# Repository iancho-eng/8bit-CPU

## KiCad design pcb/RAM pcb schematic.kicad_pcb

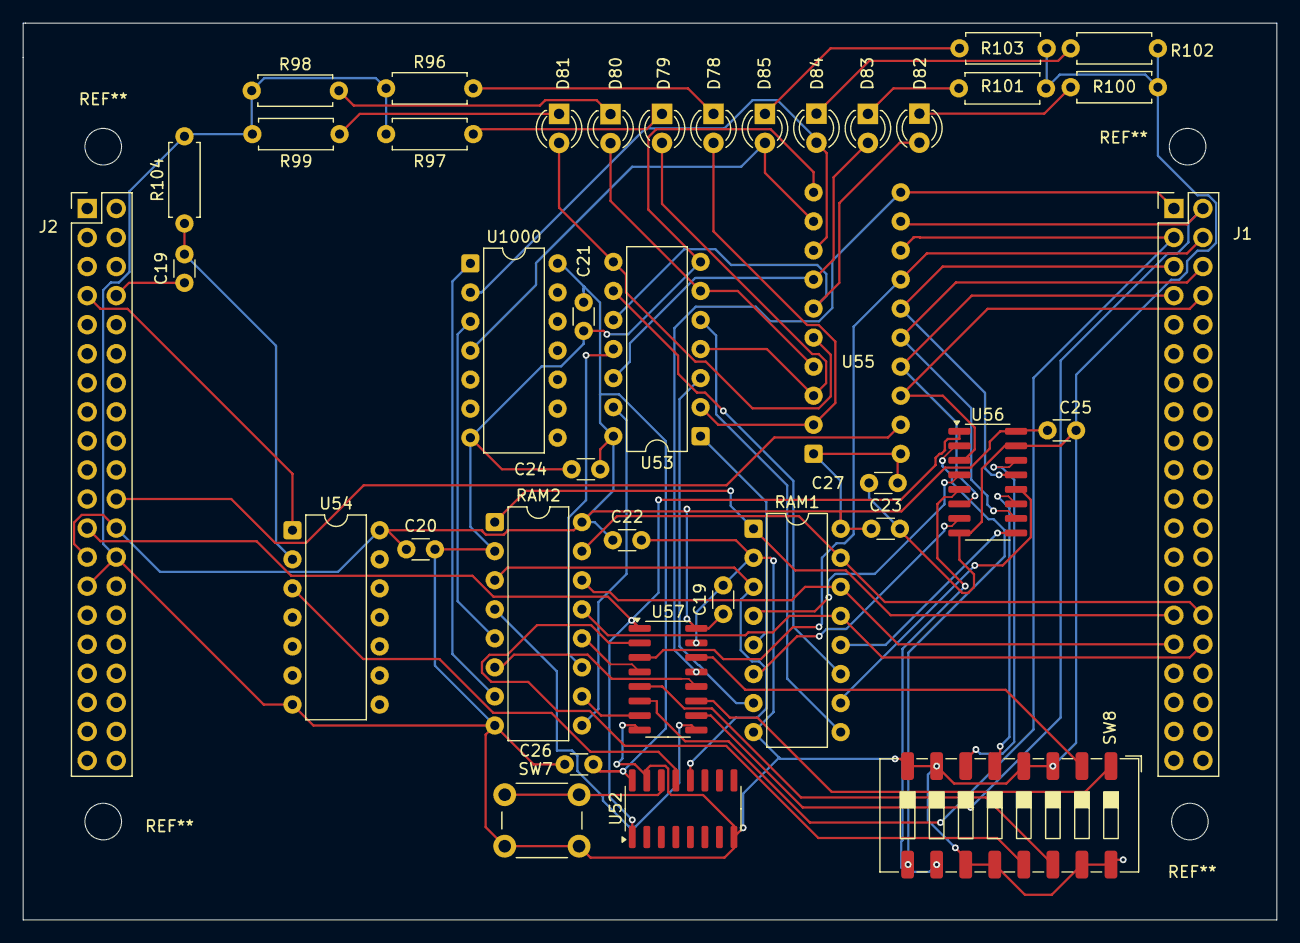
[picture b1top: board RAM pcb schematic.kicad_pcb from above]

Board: 2 copper layers, 109.6 x 78.4 mm, 40 parts (1 on the bottom side), 62 nets.

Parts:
C19, C19#2, C20, C21, C22, C23, C24, C25, C26, C27: 0.01uF; C_Disc_D3.0mm_W1.6mm_P2.50mm
D78, D79, D80, D81, D82, D83, D84, D85: RED; LED_D3.0mm
J1, J2: Conn_02x20_Odd_Even; PinHeader_2x20_P2.54mm_Vertical
R96, R97, R98, R99, R100, R101, R102, R103: 220; R_Axial_DIN0207_L6.3mm_D2.5mm_P7.62mm_Horizontal
R104: 1K; R_Axial_DIN0207_L6.3mm_D2.5mm_P7.62mm_Horizontal
RAM1, RAM2: DIP-16_W7.62mm
SW7: SW_Push; SW_PUSH_6mm
SW8: SW_DIP_x08; SW_DIP_SPSTx08_Slide_9.78x22.5mm_W8.61mm_P2.54mm
U52, U56, U57: 74HCT157D; SOIC-16_3.9x9.9mm_P1.27mm
U53, U1000: 74HCT04; DIP-14_W7.62mm
U54: 7400; DIP-14_W7.62mm
U55: 74HCT245N; DIP-20_W7.62mm

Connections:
/RAM/A0: J1.29, RAM1.1 (A₀), RAM2.1 (A₀)
/RAM/A1: J1.30, RAM1.15 (A₁), RAM2.15 (A₁)
/RAM/A2: J1.31, RAM1.14 (A₂), RAM2.14 (A₂)
/RAM/A3: J1.32, RAM1.13 (A₃), RAM2.13 (A₃)
/RAM/BUS_0: J1.1, U55.11 (B7), U57.13 (4I1)
/RAM/BUS_1: J1.2, U55.12 (B6), U57.10 (3I1)
/RAM/BUS_2: J1.3, U55.13 (B5), U57.6 (2I1)
/RAM/BUS_3: J1.4, U55.14 (B4), U57.3 (1I1)
/RAM/BUS_4: J1.5, U55.15 (B3), U56.13 (4I1)
/RAM/BUS_5: J1.6, U55.16 (B2), U56.10 (3I1)
/RAM/BUS_6: J1.7, U55.17 (B1), U56.6 (2I1)
/RAM/BUS_7: J1.8, U55.18 (B0), U56.3 (1I1)
/RAM/CLK: C19#2.1, J2.8
/RAM/PROG: J2.23, U52.1 (S), U56.1 (S), U57.1 (S)
/RAM/RI: J2.7, U54.1
/RAM/~RO: J2.22, U55.19 (~OE)
GND: C19.2, C20.2, C21.2, C22.2, C23.2, C24.1, C25.2, C26.1, C27.1, J2.26, J2.27, R96.2, R97.2, R98.2, R99.2, R100.2, R101.2, R102.2, R103.2, R104.2, RAM1.2 (~CS), RAM1.8 (GND), RAM2.2 (~CS), RAM2.8 (GND), SW7.2, SW8.3, SW8.4, SW8.7, SW8.8, SW8.11, SW8.12, SW8.15, SW8.16, U52.8 (GND), U52.15 (~E), U53.7 (GND), U54.7 (GND), U55.10 (GND), U56.8 (GND), U56.15 (~E), U57.8 (GND), U57.15 (~E), U1000.7 (GND)
unnamed: C19#2.2, R104.1, U54.2
unnamed: D78.2 (A), U53.2, U55.2 (A0)
unnamed: D78.1 (K), R96.1
unnamed: D79.2 (A), U53.4, U55.3 (A1)
unnamed: D79.1 (K), R97.1
unnamed: D80.2 (A), U53.6, U55.4 (A2)
unnamed: D80.1 (K), R98.1
unnamed: D81.2 (A), U53.8, U55.5 (A3)
unnamed: D81.1 (K), R99.1
unnamed: D82.2 (A), U53.10, U55.6 (A4)
unnamed: D82.1 (K), R100.1
unnamed: D83.2 (A), U53.12, U55.7 (A5)
unnamed: D83.1 (K), R101.1
unnamed: D84.2 (A), U55.8 (A6), U1000.2
unnamed: D84.1 (K), R102.1
unnamed: D85.2 (A), U55.9 (A7), U1000.4
unnamed: D85.1 (K), R103.1
unnamed: RAM1.4 (D₀), U56.4 (1Y)
unnamed: RAM1.6 (D₁), U56.7 (2Y)
unnamed: RAM1.10 (D₂), U56.12 (4Y)
unnamed: RAM1.12 (D₃), U56.9 (3Y)
unnamed: RAM1.5 (~O₀), U53.1
unnamed: RAM1.7 (~O₁), U53.3
unnamed: RAM1.9 (~O₂), U53.5
unnamed: RAM1.11 (~O₃), U53.9
unnamed: RAM1.3 (~WE), RAM2.3 (~WE), U52.12 (4Y)
unnamed: RAM2.4 (D₀), U57.9 (3Y)
unnamed: RAM2.6 (D₁), U57.12 (4Y)
unnamed: RAM2.10 (D₂), U57.7 (2Y)
unnamed: RAM2.12 (D₃), U57.4 (1Y)
unnamed: RAM2.5 (~O₀), U1000.3
unnamed: RAM2.7 (~O₁), U1000.1
unnamed: RAM2.9 (~O₂), U53.13
unnamed: RAM2.11 (~O₃), U53.11
unnamed: SW7.1, U52.14 (4I0)
unnamed: U52.13 (4I1), U54.3
unnamed: SW8.9, U56.2 (1I0)
unnamed: SW8.10, U56.5 (2I0)
unnamed: SW8.5, U56.11 (3I0)
unnamed: SW8.6, U56.14 (4I0)
unnamed: SW8.13, U57.2 (1I0)
unnamed: SW8.14, U57.5 (2I0)
unnamed: SW8.1, U57.11 (3I0)
unnamed: SW8.2, U57.14 (4I0)
VCC: C19.1, C20.1, C21.1, C22.1, C23.1, C24.2, C25.1, C26.2, C27.2, J2.24, J2.25, RAM1.16 (Vcc), RAM2.16 (Vcc), U52.16 (VCC), U53.14 (VCC), U54.14 (VCC), U55.1 (DIR), U55.20 (VCC), U56.16 (VCC), U57.16 (VCC), U1000.14 (VCC)

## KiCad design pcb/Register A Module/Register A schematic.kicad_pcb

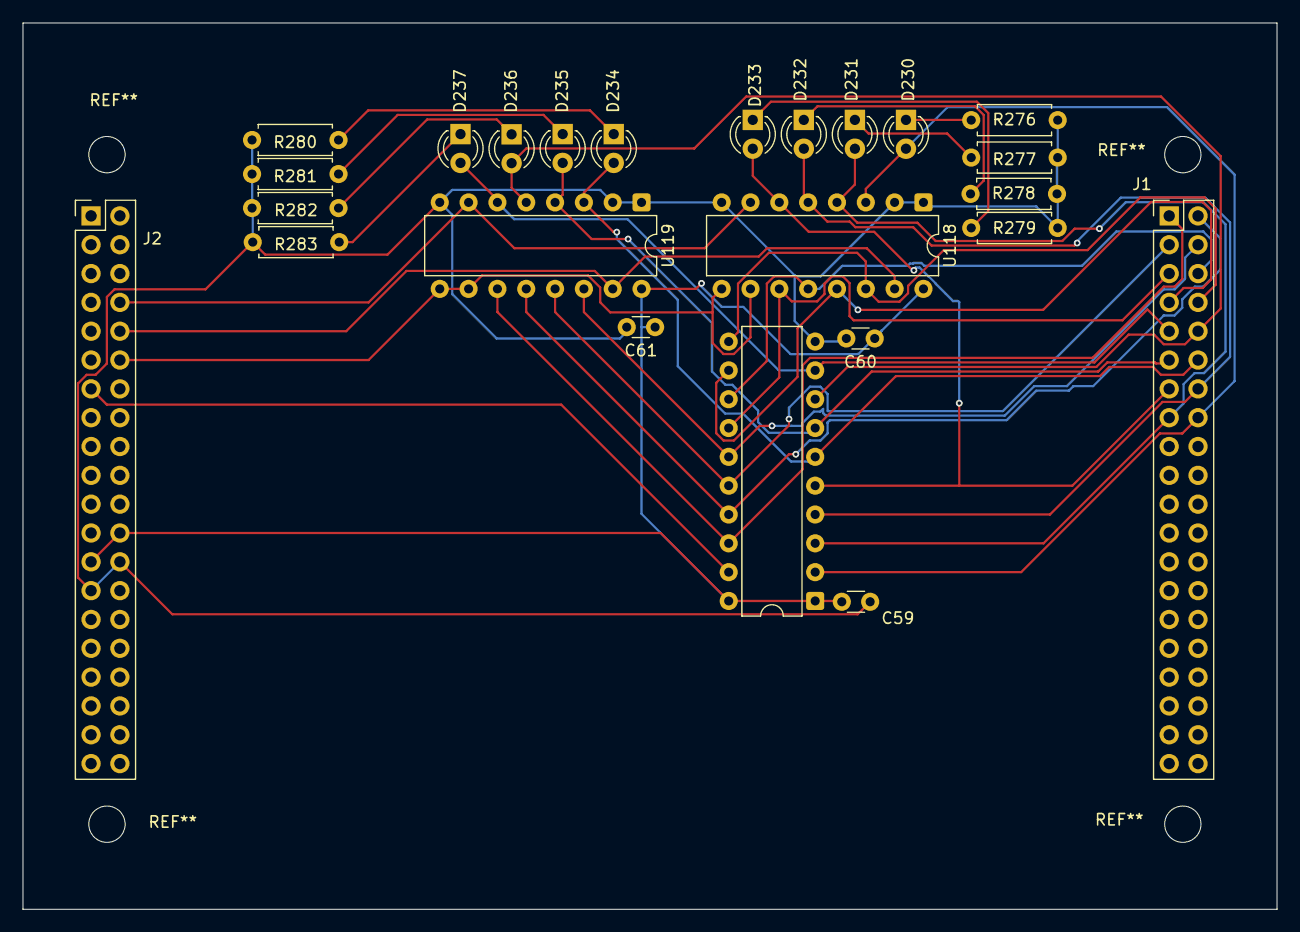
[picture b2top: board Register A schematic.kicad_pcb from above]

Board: 2 copper layers, 110.5 x 78.1 mm, 24 parts (0 on the bottom side), 30 nets.

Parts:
C59, C60, C61: 0.1uF; C_Disc_D3.0mm_W1.6mm_P2.50mm
D230, D231, D232, D233, D234, D235, D236, D237: RED; LED_D3.0mm
J1, J2: Conn_02x20_Odd_Even; PinHeader_2x20_P2.54mm_Vertical
R276, R277, R278, R279, R280, R281, R282, R283: 220; R_Axial_DIN0207_L6.3mm_D2.5mm_P7.62mm_Horizontal
U11: 74HCT245N; DIP-20_W7.62mm
U118, U119: 74HCT173; DIP-16_W7.62mm

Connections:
/Register A Module/A_0: D237.2 (A), J1.9, U11.9 (A7), U119.6 (Q3)
/Register A Module/A_1: D236.2 (A), J1.10, U11.8 (A6), U119.5 (Q2)
/Register A Module/A_2: D235.2 (A), J1.11, U11.7 (A5), U119.4 (Q1)
/Register A Module/A_3: D234.2 (A), J1.12, U11.6 (A4), U119.3 (Q0)
/Register A Module/A_4: D233.2 (A), J1.13, U11.5 (A3), U118.6 (Q3)
/Register A Module/A_5: D232.2 (A), J1.14, U11.4 (A2), U118.5 (Q2)
/Register A Module/A_6: D231.2 (A), J1.15, U11.3 (A1), U118.4 (Q1)
/Register A Module/A_7: D230.2 (A), J1.16, U11.2 (A0), U118.3 (Q0)
/Register A Module/BUS_0: J1.1, U11.18 (B0), U119.11 (D3)
/Register A Module/BUS_1: J1.2, U11.17 (B1), U119.12 (D2)
/Register A Module/BUS_2: J1.3, U11.16 (B2), U119.13 (D1)
/Register A Module/BUS_3: J1.4, U11.15 (B3), U119.14 (D0)
/Register A Module/BUS_4: J1.5, U11.14 (B4), U118.11 (D3)
/Register A Module/BUS_5: J1.6, U11.13 (B5), U118.12 (D2)
/Register A Module/BUS_6: J1.7, U11.12 (B6), U118.13 (D1)
/Register A Module/BUS_7: J1.8, U11.11 (B7), U118.14 (D0)
/Register A Module/CLK: J2.8, U118.7 (Cp), U119.7 (Cp)
/Register A Module/CLR: J2.10, U118.15 (Mr), U119.15 (Mr)
/Register A Module/~AI: J2.12, U118.9 (E1), U118.10 (E2), U119.9 (E1), U119.10 (E2)
/Register A Module/~AO: J2.13, U11.19 (~OE)
GND: C59.2, C60.2, C61.2, J2.26, J2.27, R276.2, R277.2, R278.2, R279.2, R280.2, R281.2, R282.2, R283.2, U11.10 (GND), U118.1 (Oe1), U118.2 (Oe2), U118.8 (GND), U119.1 (Oe1), U119.2 (Oe2), U119.8 (GND)
unnamed: D230.1 (K), R276.1
unnamed: D231.1 (K), R277.1
unnamed: D232.1 (K), R278.1
unnamed: D233.1 (K), R279.1
unnamed: D234.1 (K), R280.1
unnamed: D235.1 (K), R281.1
unnamed: D236.1 (K), R282.1
unnamed: D237.1 (K), R283.1
VCC: C59.1, C60.1, C61.1, J2.24, J2.25, U11.1 (DIR), U11.20 (VCC), U118.16 (VCC), U119.16 (VCC)
